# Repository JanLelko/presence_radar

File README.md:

<div align="center">

# Presence Radar

Radarowy czujnik obecności, upadków i zasiedzenia.
ESP32-C6 + Acconeer XM125 (A121), MQTT, panel w przeglądarce.

</div>

---

## Opis

Firmware ESP-IDF dla ESP32-C6 odczytuje radar XM125 przez I2C, lokalnie klasyfikuje
zdarzenia (obecność, upadek, zasiedzenie, przegrzanie) i publikuje wynik w JSON do brokera MQTT.
Dashboard w przeglądarce (MQTT over WebSockets) wyświetla stan pokoi na żywo.

- Wi-Fi i adres brokera ustawiane przez Captive Portal, zapis w NVS.
- Parametry radaru i progi alarmów zmieniane z panelu przez MQTT, bez ponownego wgrywania firmware.
- Sygnalizacja stanu: LED RGB (WS2812), dioda na PCB, buzzer.

<div align="center">

<sub>Panel (dashboard)</sub>

<sub>Urządzenie</sub>

</div>

## Architektura

```mermaid
flowchart LR
    R["XM125 (A121 + STM32)"] -- "I2C 0x52" --> E["ESP32-C6"]
    E -- "MQTT" --> B[("Mosquitto 1883 / 9001 WS")]
    B -- "WebSockets" --> D["Dashboard"]
    D -- "cfg / cmd" --> B
    B --> E
```

### Tematy MQTT

| Temat | Kierunek | Retained | Zawartość |
| :-- | :-- | :-: | :-- |
| `pokoj/101/radar` | urządzenie → panel | tak | Pomiar i alarm |
| `pokoj/101/cfg` | panel → urządzenie | tak | Zmiany konfiguracji (`radar`, `edge`) |
| `pokoj/101/cfg/state` | urządzenie → panel | tak | Stan raportowany konfiguracji |
| `pokoj/101/cmd` | panel → urządzenie | tak | Polecenia, np. `{"armed":true}` |
| `pokoj/101/status` | urządzenie → panel | tak | `{"st":"online"}` / `{"st":"offline"}` (LWT) |

Przykład ramki `pokoj/101/radar`:

```json
{"obecnosc": 1, "odleglosc": 2310, "mikro": 1450, "makro": 220, "temp": 41, "alarm": "OK"}
```

`alarm`: `OK`, `POZAR`, `UPADEK`, `ZASIEDZENIE`. Publikacja co 2 s, przy alarmie natychmiast.

## Uruchomienie

Wymagania: Linux, ESP-IDF (`~/main/tools/esp-idf`), Mosquitto. Target: **ESP32-C6**.

```bash
. $HOME/main/tools/esp-idf/export.sh        # w każdym nowym terminalu
idf.py set-target esp32c6                   # raz na świeży katalog build
idf.py -p /dev/ttyACM0 build flash monitor  # wyjście z monitora: Ctrl+]

mosquitto -c mosquitto.conf -v              # broker (1883 + 9001 WS)
firefox dashboard/index.html                # panel, bez serwera HTTP
```

`idf.py` uruchamiaj z korzenia projektu, nie z `main/`.

### Pierwsza konfiguracja

1. Przy pustym NVS urządzenie uruchamia otwartą sieć `Konfiguracja_Radaru` (`192.168.4.1`).
2. Połącz się z nią telefonem. Portal otworzy się automatycznie, w przeciwnym razie wejdź na `http://192.168.4.1`.
3. Podaj SSID, hasło i adres brokera (np. `mqtt://10.42.0.1:1883`). Urządzenie zrestartuje się i połączy.

Reset konfiguracji: przytrzymaj przycisk (GPIO 9) przez ok. 3 s. Dane sieci i MQTT zostaną usunięte z NVS, urządzenie wróci do portalu.

## Sprzęt

| ESP32-C6 | Radar / element | Uwagi |
| :-- | :-- | :-- |
| 5V | 5V | Zasilanie |
| GND | GND | Masa |
| GPIO 2 | SDA | I2C |
| GPIO 11 | SCL | I2C, 100 kHz |
| 3.3V | WAKE_UP | **Wymagane.** Bez tego STM32 śpi, a I2C zwraca same zera |
| GPIO 10 | INT | Niewykorzystane |
| GPIO 8 | WS2812 | LED RGB na płytce DevKitC-1 |
| GPIO 18 | LED | Dioda alarmowa |
| GPIO 9 | Przycisk | Do GND, pull-up wewnętrzny |
| GPIO 3 | Buzzer | |

Piny zdefiniowane w `main/board_pins.h`. Schemat i PCB (KiCad): `hardware/radar_xm125_esp32c6/`.

### Firmware radaru (STM32)

Moduł musi działać jako serwer I2C „Presence Detector”. Wgranie narzędziem Acconeer Exploration Tool:

```bash
python3 -m venv .venv && source .venv/bin/activate
pip install "acconeer-exptool[app]"
python -m acconeer.exptool.app
```

1. Tryb bootloadera: przytrzymaj `BOOT`, naciśnij `RST`, puść `BOOT`.
2. Zakładka **Flash**, wybierz port (`/dev/ttyACM0`), wgraj [`firmware/xm125/i2c_presence_detector.bin`](firmware/xm125/i2c_presence_detector.bin).

## Protokół I2C

Adres `0x52`. Rejestry 16-bitowe (MSB first), wartości 32-bitowe big-endian, transfery w wielokrotnościach 4 bajtów.

| Rejestr | R/W | Opis |
| :-- | :-: | :-- |
| `0x0000` | R | Wersja firmware (same zera: brak WAKE_UP) |
| `0x0003` | R | Status detektora (`0xFF`: gotowy, niewystartowany) |
| `0x0010` | R | Wynik: 4 × u32 (16 bajtów) |
| `0x0100` | W | Komenda: `1` apply config, `2` start, `3` stop |

Inicjalizacja: `1`, następnie `2` do `0x0100`. Odczyt z `0x0010`:

| Bajty | Pole | Znaczenie |
| :-- | :-- | :-- |
| 0-3 | `presence_reg` | bit 0: obecność; bity 16-31: temperatura chipa |
| 4-7 | `distance_mm` | Odległość [mm] |
| 8-11 | `intra_score` | Energia ruchu szybkiego |
| 12-15 | `inter_score` | Energia ruchu wolnego |

Parametry konfiguracji radaru: [`docs/parametry_radaru.md`](docs/parametry_radaru.md).

## Logika alarmów

Klasyfikacja co 250 ms. Progi (sekcja `edge` w `pokoj/101/cfg`) zapisywane w NVS.

| Parametr | Domyślnie | Zakres | Opis |
| :-- | :-: | :-: | :-- |
| `podloga_mm` | 2500 | 1000-6000 | Odległość radar-podłoga [mm] |
| `prog_upadku` | 1500 | 0-5000 | Minimalny `intra_score` dla upadku |
| `max_temp_c` | 20 | 0-90 | Próg temperatury [°C]; 20 to wartość demonstracyjna |
| `zasiedzenie_s` | 300 | 10-3600 | Czas obecności bez ruchu do alarmu [s] |

| Alarm | Warunek |
| :-- | :-- |
| `POZAR` | `temp > max_temp_c` |
| `UPADEK` | `intra_score > prog_upadku` i `distance_mm > podloga_mm - 400` |
| `ZASIEDZENIE` | Obecność z niskim `intra` i wysokim `inter` przez `zasiedzenie_s` |
| `OK` | Pozostałe przypadki |

Dashboard: przełącznik **Alarm** uzbraja sygnał dźwiękowy i baner przy braku obecności lub utracie łączności.
Brak danych dłuższy niż 10 s oznacza stan OFFLINE karty pokoju.

## Struktura

```
main/
  main.c            pętla radaru, klasyfikator alarmów, MQTT
  radar.c           warstwa I2C XM125
  radar_cfg.c       model konfiguracji radaru
  edge_cfg.c        progi alarmów (NVS)
  wifi_mqtt.c       Wi-Fi (STA/SoftAP), NVS, klient MQTT
  captive_portal.c  portal konfiguracji
  dns_server.c      DNS przekierowujący na portal
  status_led.c      sygnalizacja LED
  board_pins.h      definicje pinów
dashboard/          panel (index.html)
docs/               dokumentacja i raport końcowy
firmware/xm125/     gotowy firmware STM32 radaru (.bin)
hardware/           projekt KiCad
examples/           narzędzia pomocnicze (poza buildem)
mosquitto.conf      porty 1883 i 9001
quickstart.sh       broker + ESP-IDF + dashboard
```

Plany i ograniczenia: [`TODO.md`](TODO.md).

## Rozwiązywanie problemów

| Objaw | Przyczyna / rozwiązanie |
| :-- | :-- |
| `Permission denied` na `/dev/ttyACM0` | `sudo chmod 666 /dev/ttyACM0` |
| Błędy CMake | `idf.py` uruchomiony poza korzeniem projektu; ewentualnie `rm -rf build/` |
| I2C zwraca same zera | WAKE_UP niepodłączony do 3.3V |
| Odległości rzędu `4008635904` lub brak reakcji | Radar nie wystartował; sprawdź komendę `2` do `0x0100` |
| Brak strony konfiguracji | Wejdź na `http://192.168.4.1`; brak hotspotu oznacza dane w NVS, wykonaj reset przyciskiem |
| Brak publikacji MQTT | Błędne SSID/hasło lub nieosiągalny broker; sprawdź log szeregowy |

## Źródła

- [Waveshare A121 Range Sensor](https://www.waveshare.com/wiki/A121_Range_Sensor#Documents)
- [Acconeer Exploration Tool](https://docs.acconeer.com/en/latest/exploration_tool/index.html)
- [ESP32-C6-WROOM-1 datasheet](https://documentation.espressif.com/esp32-c6-wroom-1_wroom-1u_datasheet_en.html)
- [ESP-IDF I2C API](https://docs.espressif.com/projects/esp-idf/en/stable/api-reference/peripherals/i2c.html)

## Licencja

Kod źródłowy: [MIT](LICENSE). Plik `firmware/xm125/i2c_presence_detector.bin` jest dziełem Acconeer
i podlega licencji z [`firmware/xm125/LICENSE-Acconeer.txt`](firmware/xm125/LICENSE-Acconeer.txt).

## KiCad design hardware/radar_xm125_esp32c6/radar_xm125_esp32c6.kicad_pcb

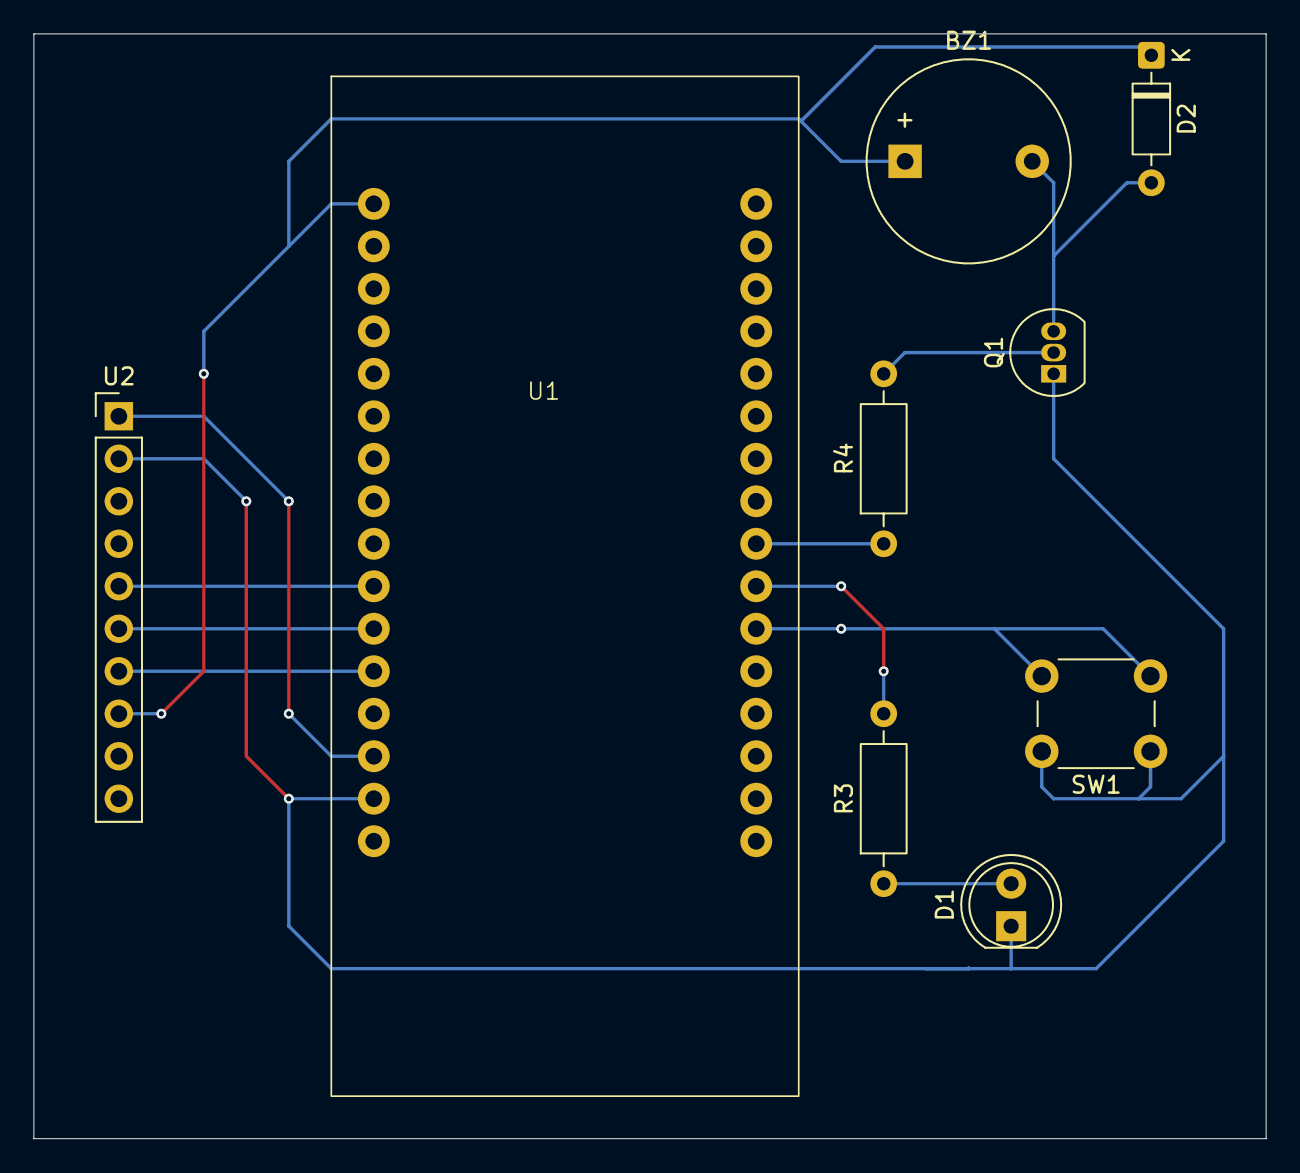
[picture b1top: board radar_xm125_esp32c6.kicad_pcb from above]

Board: 2 copper layers, 73.7 x 66.0 mm, 9 parts (0 on the bottom side), 12 nets.

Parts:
BZ1: Buzzer; Buzzer_12x9.5RM7.6
D1: LED; LED_D5.0mm
D2: 1N4148; D_DO-35_SOD27_P7.62mm_Horizontal
Q1: 2N2222A331; TO-92_Inline
R3: 330; R_Axial_DIN0207_L6.3mm_D2.5mm_P10.16mm_Horizontal
R4: 1k; R_Axial_DIN0207_L6.3mm_D2.5mm_P10.16mm_Horizontal
SW1: SW_Push; SW_PUSH_6mm_H5mm
U1: ESP32_C6_WROOM_1_DEV; ESP32_C6_Devkit
U2: Waveshare_A121_Radar; PinHeader_1x10_P2.54mm_Vertical

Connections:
+3.3V: BZ1.1 (+), D2.1 (K), U1.1 (3V3), U2.8 (WAKE_UP)
+5V: U1.14 (5V), U2.1 (5V)
/BUTTON: SW1.2, U1.27 (GPIO9)
/BUZZER: R4.1, U1.25 (GPIO19)
/LED_STATUS: R3.2, U1.26 (GPIO18)
/MCU_INT: U1.12 (GPIO2), U2.7 (MCU_INT)
/SCL: U1.11 (GPIO11), U2.6 (SCL)
/SDA: U1.10 (GPIO10), U2.5 (SDA)
GND: D1.1 (K), Q1.1 (E), SW1.1, U1.15 (GND), U2.2 (GND)
unnamed: BZ1.2 (-), D2.2 (A), Q1.3 (C)
unnamed: D1.2 (A), R3.1
unnamed: Q1.2 (B), R4.2

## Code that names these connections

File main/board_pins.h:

#ifndef BOARD_PINS_H
#define BOARD_PINS_H

/*
 * Jedyne miejsce w projekcie z numerami pinów GPIO ESP32-C6.
 *
 * Historycznie piny były rozsiane po main.c, radar.c (z BŁĘDNYM SDA=GPIO10 —
 * to linia INT radaru) i status_led.c. Trzymanie ich tutaj sprawia, że rozjazd
 * typu "SDA na GPIO2 czy GPIO10?" jest strukturalnie niemożliwy.
 *
 * Layout płytki (patrz też README §1 i hardware/):
 *   I2C do modułu XM125: SDA=GPIO2, SCL=GPIO11, 100 kHz, wewn. pull-upy.
 */

#define PIN_I2C_SDA     2    // XM125 SDA
#define PIN_I2C_SCL     11   // XM125 SCL
#define PIN_RADAR_INT   10   // XM125 INT (MCU_INT) — podłączone, na razie nieużywane w kodzie
#define PIN_RGB         8    // wbudowany WS2812 na DevKitC-1 (status_led.c)
#define PIN_LED         18   // dioda alarmowa na PCB — miga w lockstep z RGB (status_led.c)
#define PIN_BUTTON      9    // przycisk między GPIO9 a GND, wewn. pull-up (wciśnięty = 0)
#define PIN_BUZZER      3    // buzzer alarmu

#endif /* BOARD_PINS_H */

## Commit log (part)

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2026-05-12 Initial commit: ESP32-C6 I2C driver for Acconeer XM125 presence radar
2026-05-12 chore: rename example_tests to examples
2026-05-12 chore: remove leftover example_tests directory
2026-05-21 refactor: split firmware into components, add KiCad hardware project
2026-06-08 feat: Wi-Fi provisioning via captive portal
    Szczegóły poprawek:
    - Dodano obsługę dekodowania URL dla znaków specjalnych w adresie MQTT.
    - Zoptymalizowano funkcję load_credentials z bezpiecznym odczytem pamięci NVS.
    - Usunięto błędy multiple definition dla zmiennej mqtt_client.
    - Zablokowano próbę łączenia z Wi-Fi przy pustym haśle (puste ciągi w NVS).
2026-06-25 feat: DNS-based captive portal auto-popup and docs update
2026-06-26 feat(dashboard): alarm switch and connection-loss detection
    Switch 'Alarm' w panelu: gdy uzbrojony i brak obecnosci pod czujnikiem
    -> dzwiek (Web Audio) + czerwony baner. Watchdog oznacza karty jako
    OFFLINE przy braku danych >10 s lub padzie brokera; przy uzbrojonym
    alarmie utrata lacznosci wyje tak samo jak brak obecnosci.
2026-06-26 feat: reset stored config with BOOT button and return to captive portal
    Przytrzymanie przycisku (GPIO9) ~3 s kasuje zapisana siec/MQTT z NVS
    i restartuje urzadzenie do captive portala (3x sygnal buzzer+dioda).
    Usunieto martwa, niezarejestrowana funkcje wifi_event_handler.
2026-06-26 chore: ignore KiCad artifacts and untrack them
    Autosave, backupy (*-backups/), fp-info-cache, locki, *.bak,
    *.kicad_sch-bak oraz *.kicad_prl przestaja byc wersjonowane.
    Pliki pozostaja na dysku (git rm --cached). W repo zostaje realny
    projekt: .kicad_pcb/.sch/.pro/.sym + tabele bibliotek + footprint.
2026-06-26 docs: update README and TODO with new features
    - README: sekcja o przelaczniku Alarm + wykrywaniu OFFLINE/utraty lacznosci,
    icon.svg w strukturze, wzmianka o nowym wygladzie portalu.
    - TODO: sekcja Zrobione (czerwiec 2026), odhaczone pkt 1 (DNS/auto-popup),
    pkt 5 (offline != pusty pokoj), reset przyciskiem, martwa funkcja; kolejnosc
    przepisana na to, co zostalo.
2026-06-29 feat: LED synchronization, dashboard improvements and RGB status signalling
    Firmware:
    - status_led.c przejmuje diode na PCB (GPIO18) i miga nia w lockstep z
    wbudowanym RGB (GPIO8) - ta sama czestotliwosc i faza; w main.c zostal
    tylko buzzer. Pin oddawany przy wyjsciu z alarmu i przed sygnalem resetu.
    - MAX_TEMP obnizone 60 -> 20 (prog POZARU wyzwalany chuchnieciem, demo).
    Dashboard:
